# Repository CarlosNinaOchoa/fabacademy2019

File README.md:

<h1>Fab Academy Repo (Carlos Nina Ochoa)</h1>
<h2>This is a repo of the files created during my assignments on Fab academy 2019.</h2>
<p>To see my website, with more information about the files, please visit: http://fabacademy.org/2019/labs/tecsup/students/carlos-ochoa/ </p>

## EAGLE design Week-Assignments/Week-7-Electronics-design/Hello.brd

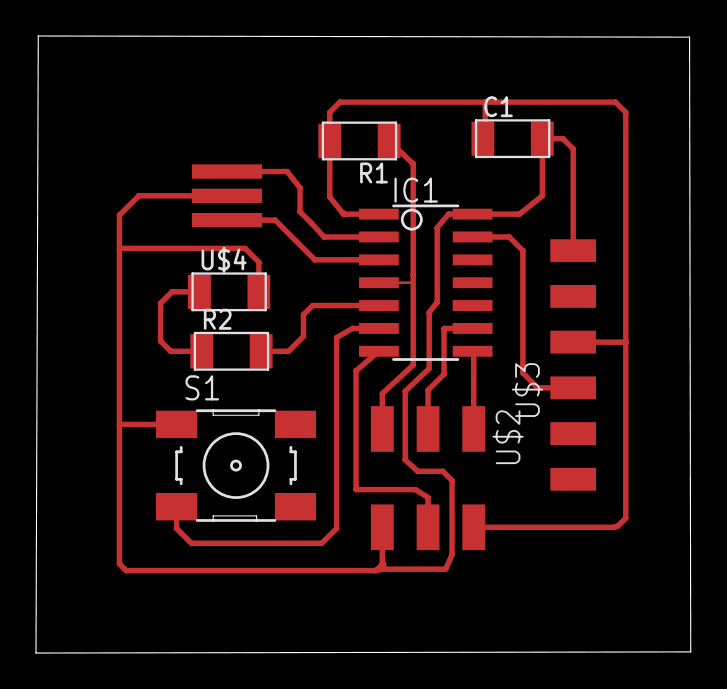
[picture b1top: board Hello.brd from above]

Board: 2 copper layers, 36.4 x 34.3 mm, 9 parts (0 on the bottom side), 12 nets.

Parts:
C1: CAP-US1206FAB; C1206FAB
IC1: ATTINY44-SSU; SOIC14
R1, R2: R1206FAB
S1: 6MM_SWITCH
U$1: RESONATOR; EFOBM
U$2: AVRISPSMD; 2X03SMD
U$3: FTDI-SMD-HEADER; 1X06SMD
U$4: LEDFAB1206; LED1206FAB

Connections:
GND: C1.2, IC1.14, S1.1, U$1.2, U$2.6, U$3.1, U$4.2
MISO: IC1.8, U$2.1
MOSI: IC1.7, U$2.4
unnamed: IC1.2, U$1.1
unnamed: IC1.3, U$1.3
unnamed: R2.1, U$4.1
unnamed: IC1.6, S1.3
unnamed: IC1.5, R2.2
PA0: IC1.13, U$3.4
RST: IC1.4, R1.1, U$2.5
SCK: IC1.9, U$2.3
VCC: C1.1, IC1.1, R1.2, U$2.2, U$3.3

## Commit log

2019-02-27 uploading 2018 previous content
